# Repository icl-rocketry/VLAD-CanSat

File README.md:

# VLAD-CanSat
Repository Containing the hardware and firmware of VLAD, a stabby boi who will participate in the Mach-21 CanSat competition

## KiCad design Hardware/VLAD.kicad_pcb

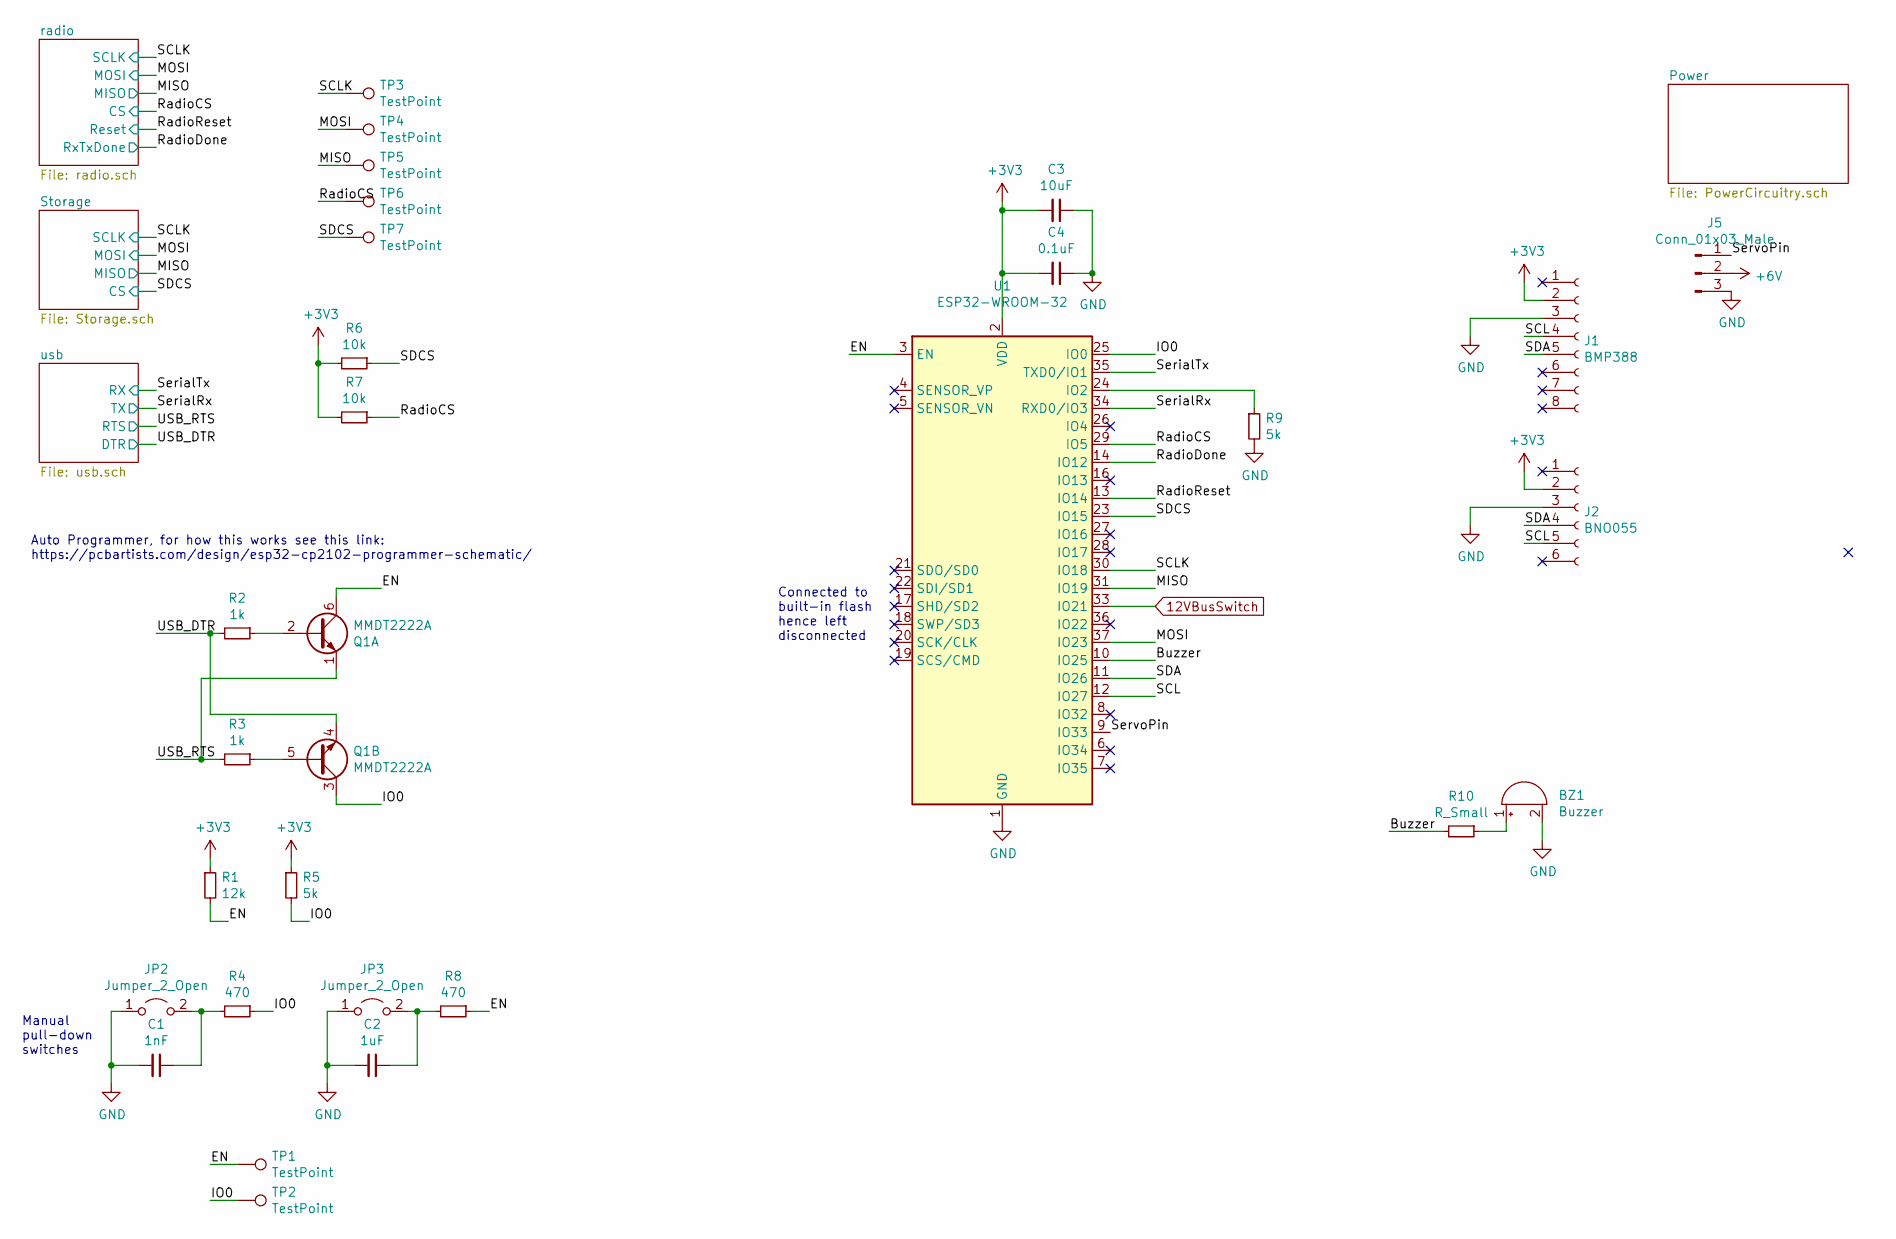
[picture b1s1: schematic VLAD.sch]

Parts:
BZ1: Buzzer; PinHeader_2x01_P2.54mm_Vertical
C1: 1nF; C_0603_1608Metric
C2: 1uF; C_0603_1608Metric
C3: 10uF; C_0603_1608Metric
C4: 0.1uF; C_0603_1608Metric
J1: BMP388; PinSocket_1x08_P2.54mm_Vertical
J2: BNO055; PinSocket_1x06_P2.54mm_Vertical
J5: Conn_01x03_Male; PinHeader_1x03_P2.54mm_Vertical
JP2, JP3: Jumper_2_Open; PinHeader_1x02_P2.54mm_Vertical
Q1: MMDT2222A; SOT-363_SC-70-6
R1: 12k; R_0603_1608Metric
R2, R3: 1k; R_0603_1608Metric
R4, R8: 470; R_0603_1608Metric
R5, R9: 5k; R_0603_1608Metric
R6, R7: 10k; R_0603_1608Metric
R10: R_Small; R_0603_1608Metric
TP1, TP2, TP3, TP4, TP5, TP6, TP7: TestPoint; TestPoint_THTPad_1.5x1.5mm_Drill0.7mm
U1: ESP32-WROOM-32

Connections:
12VBusSwitch: U1.33 (IO21); also elsewhere on the board
+3V3: C3.2, C4.2, J1.2, J2.2, R1.1, R5.1, R6.2, R7.2, U1.2 (VDD); also elsewhere on the board
+6V: J5.2; also elsewhere on the board
/Buzzer: R10.2, U1.10 (IO25)
/EN: Q1.6 (C1), R1.2, R8.1, TP1.1, U1.3 (EN)
/IO0: Q1.3 (C2), R4.1, R5.2, TP2.1, U1.25 (IO0)
/MISO: TP5.1, U1.31 (IO19); also elsewhere on the board
/MOSI: TP4.1, U1.37 (IO23); also elsewhere on the board
/RadioCS: R7.1, TP6.1, U1.29 (IO5); also elsewhere on the board
/RadioDone: U1.14 (IO12); also elsewhere on the board
/RadioReset: U1.13 (IO14); also elsewhere on the board
/SCL: J1.4, J2.5, U1.12 (IO27)
/SCLK: TP3.1, U1.30 (IO18); also elsewhere on the board
/SDA: J1.5, J2.4, U1.11 (IO26)
/SDCS: R6.1, TP7.1, U1.23 (IO15); also elsewhere on the board
/SerialRx: U1.34 (RXD0/IO3); also elsewhere on the board
/SerialTx: U1.35 (TXD0/IO1); also elsewhere on the board
/ServoPin: J5.1, U1.9 (IO33)
/USB_DTR: Q1.4 (E2), R2.2; also elsewhere on the board
/USB_RTS: Q1.1 (E1), R3.2; also elsewhere on the board
GND: BZ1.2 (+), C1.2, C2.2, C3.1, C4.1, J1.3, J2.3, J5.3, JP2.1 (A), JP3.1 (A), R9.2, U1.1 (GND), U1.15 (GND), U1.38 (GND), U1.39 (GND); also elsewhere on the board
unnamed: BZ1.1 (-), R10.1
unnamed: C1.1, JP2.2 (B), R4.2
unnamed: C2.1, JP3.2 (B), R8.2
unnamed: Q1.2 (B1), R2.1
unnamed: Q1.5 (B2), R3.1
unnamed: R9.1, U1.24 (IO2)

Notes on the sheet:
Connected to built-in flash hence left disconnected
Auto Programmer, for how this works see this link: https://pcbartists.com/design/esp32-cp2102-programmer-schematic/
Manual pull-down switches

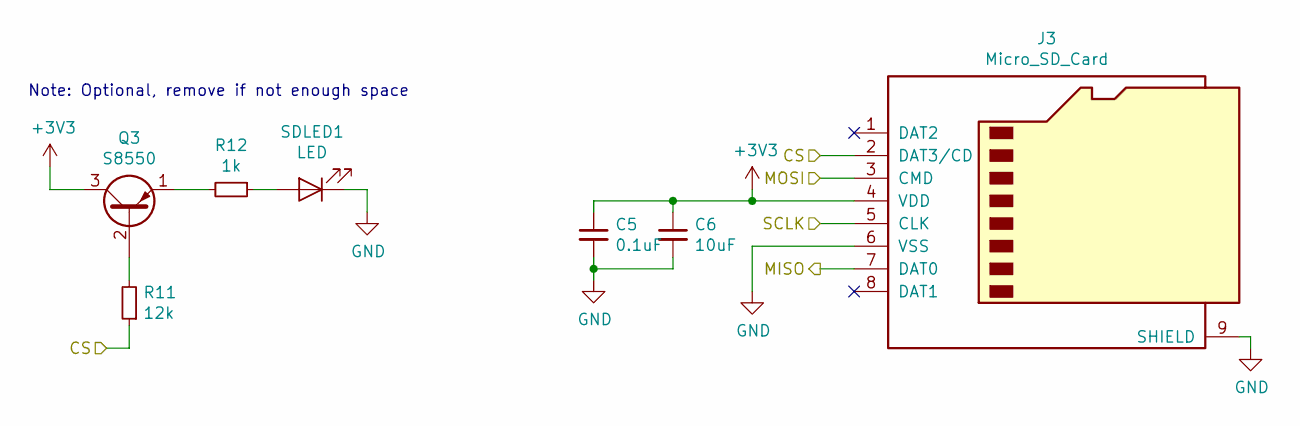
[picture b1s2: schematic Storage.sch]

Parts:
C5: 0.1uF; C_0603_1608Metric
C6: 10uF; C_0603_1608Metric
J3: Micro_SD_Card; microSD_HC_Hirose_DM3AT-SF-PEJM5
Q3: S8550; TO-92_Inline
R11: 12k; R_0603_1608Metric
R12: 1k; R_0603_1608Metric
SDLED1: LED; LED_0603_1608Metric

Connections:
+3V3: C5.1, C6.1, J3.4 (VDD), Q3.3 (C); also elsewhere on the board
/MISO: J3.7 (DAT0); also elsewhere on the board
/MOSI: J3.3 (CMD); also elsewhere on the board
/SCLK: J3.5 (CLK); also elsewhere on the board
/SDCS: J3.2 (DAT3/CD), R11.1; also elsewhere on the board
GND: C5.2, C6.2, J3.6 (VSS), J3.9 (SHIELD), SDLED1.1 (K); also elsewhere on the board
unnamed: Q3.1 (E), R12.2
unnamed: Q3.2 (B), R11.2
unnamed: R12.1, SDLED1.2 (A)

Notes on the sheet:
Note: Optional, remove if not enough space

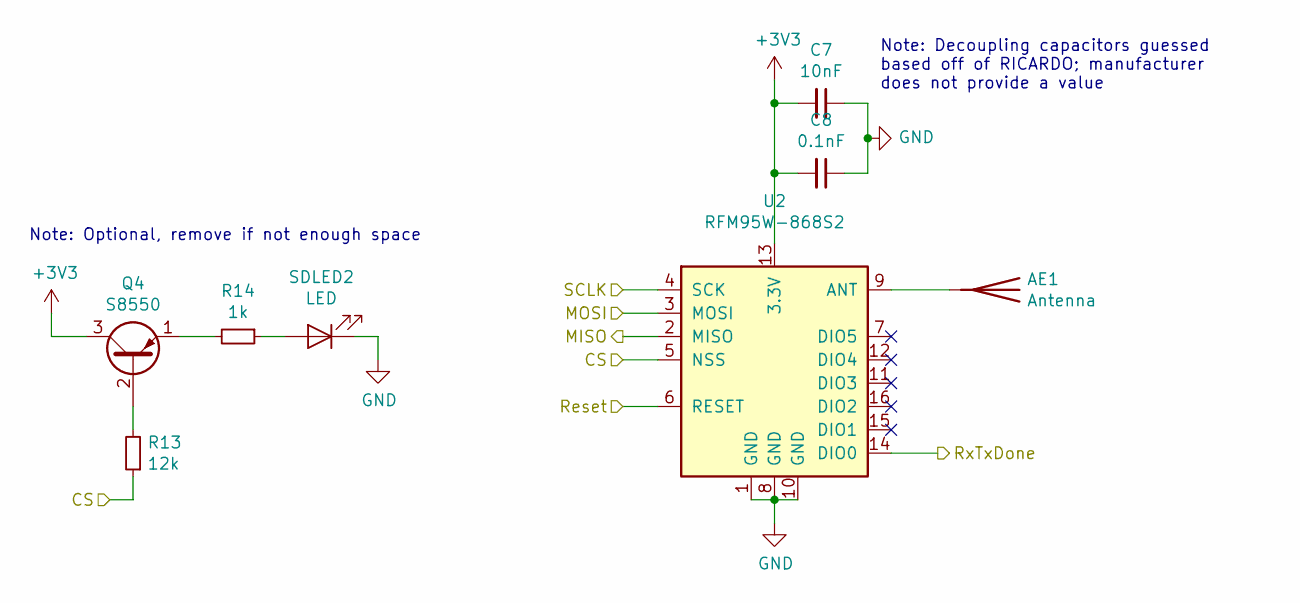
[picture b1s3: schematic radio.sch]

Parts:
AE1: Antenna; Pin_D1.1mm_L8.5mm_W2.5mm_FlatFork
C7: 10nF; C_0603_1608Metric
C8: 0.1nF; C_0603_1608Metric
Q4: S8550; TO-92_Inline
R13: 12k; R_0603_1608Metric
R14: 1k; R_0603_1608Metric
SDLED2: LED; LED_0603_1608Metric
U2: RFM95W-868S2; HOPERF_RFM9XW_SMD

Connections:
+3V3: C7.2, C8.2, Q4.3 (C), U2.13 (3.3V); also elsewhere on the board
/MISO: U2.2 (MISO); also elsewhere on the board
/MOSI: U2.3 (MOSI); also elsewhere on the board
/RadioCS: R13.1, U2.5 (NSS); also elsewhere on the board
/RadioDone: U2.14 (DIO0); also elsewhere on the board
/RadioReset: U2.6 (RESET); also elsewhere on the board
/SCLK: U2.4 (SCK); also elsewhere on the board
GND: C7.1, C8.1, SDLED2.1 (K), U2.1 (GND), U2.8 (GND), U2.10 (GND); also elsewhere on the board
unnamed: AE1.1, U2.9 (ANT)
unnamed: Q4.1 (E), R14.2
unnamed: Q4.2 (B), R13.2
unnamed: R14.1, SDLED2.2 (A)

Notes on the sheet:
Note: Decoupling capacitors guessed based off of RICARDO; manufacturer does not provide a value
Note: Optional, remove if not enough space

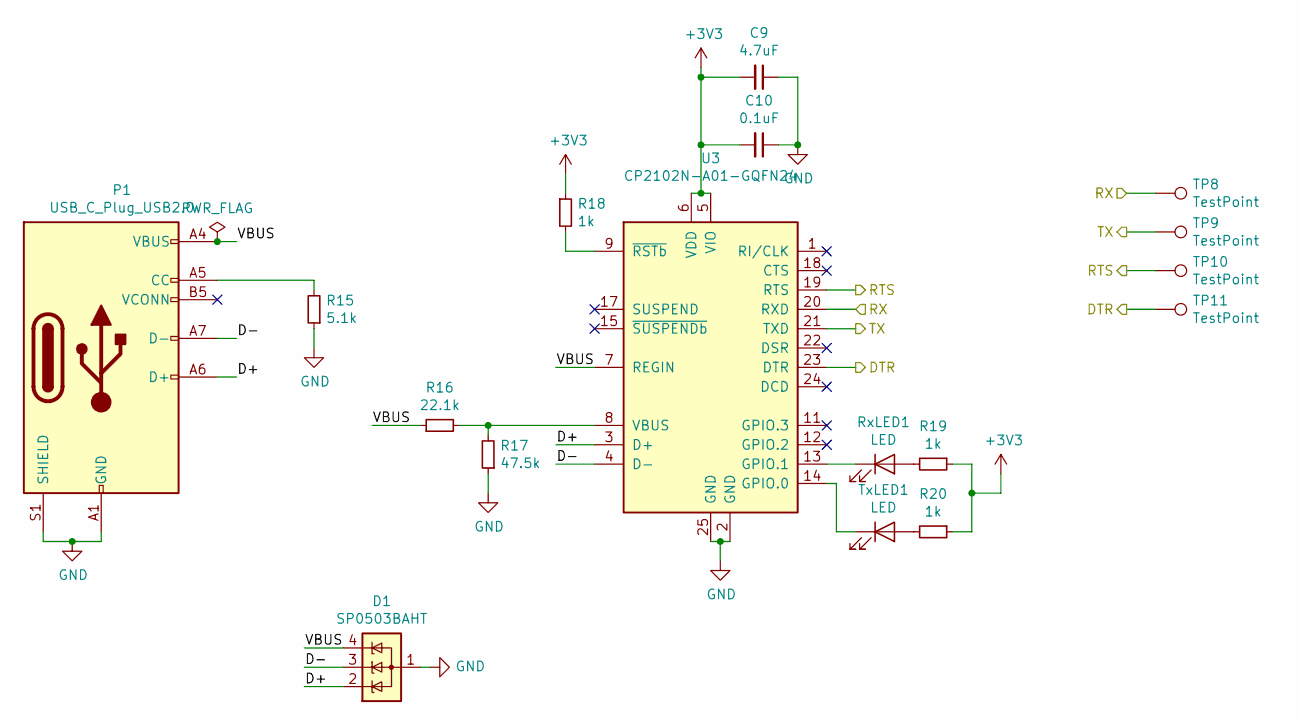
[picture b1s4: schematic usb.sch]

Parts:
C9: 4.7uF; C_0603_1608Metric
C10: 0.1uF; C_0603_1608Metric
D1: SP0503BAHT; SOT-143
P1: USB_C_Plug_USB2.0; USB_C_Receptacle_GCT_USB4085
R15: 5.1k; R_0603_1608Metric
R16: 22.1k; R_0603_1608Metric
R17: 47.5k; R_0603_1608Metric
R18, R19, R20: 1k; R_0603_1608Metric
RxLED1: LED; LED_0603_1608Metric
TP8, TP9, TP10, TP11: TestPoint; TestPoint_THTPad_1.5x1.5mm_Drill0.7mm
TxLED1: LED; LED_0603_1608Metric
U3: CP2102N-A01-GQFN24; QFN-24-1EP_4x4mm_P0.5mm_EP2.6x2.6mm

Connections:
+3V3: C9.2, C10.2, R18.1, R19.1, R20.1, U3.5 (VIO), U3.6 (VDD); also elsewhere on the board
/SerialRx: TP9.1, U3.21 (TXD); also elsewhere on the board
/SerialTx: TP8.1, U3.20 (RXD); also elsewhere on the board
/USB_DTR: TP11.1, U3.23 (DTR); also elsewhere on the board
/USB_RTS: TP10.1, U3.19 (RTS); also elsewhere on the board
/usb/D+: D1.2 (K), P1.A6 (D+), U3.3 (D+)
/usb/D-: D1.3 (K), P1.A7 (D-), U3.4 (D-)
/usb/VBUS: D1.4 (K), P1.A4 (VBUS), P1.A9 (VBUS), P1.B4 (VBUS), P1.B9 (VBUS), R16.1, U3.7 (REGIN)
GND: C9.1, C10.1, D1.1 (A), P1.A1 (GND), P1.A12 (GND), P1.B1 (GND), P1.B12 (GND), P1.S1 (SHIELD), R15.1, R17.1, U3.2 (GND), U3.25 (GND); also elsewhere on the board
unnamed: P1.A5 (CC), R15.2
unnamed: R16.2, R17.2, U3.8 (VBUS)
unnamed: R18.2, U3.9 (~RSTb)
unnamed: R19.2, RxLED1.2 (A)
unnamed: R20.2, TxLED1.2 (A)
unnamed: RxLED1.1 (K), U3.13 (GPIO.1)
unnamed: TxLED1.1 (K), U3.14 (GPIO.0)

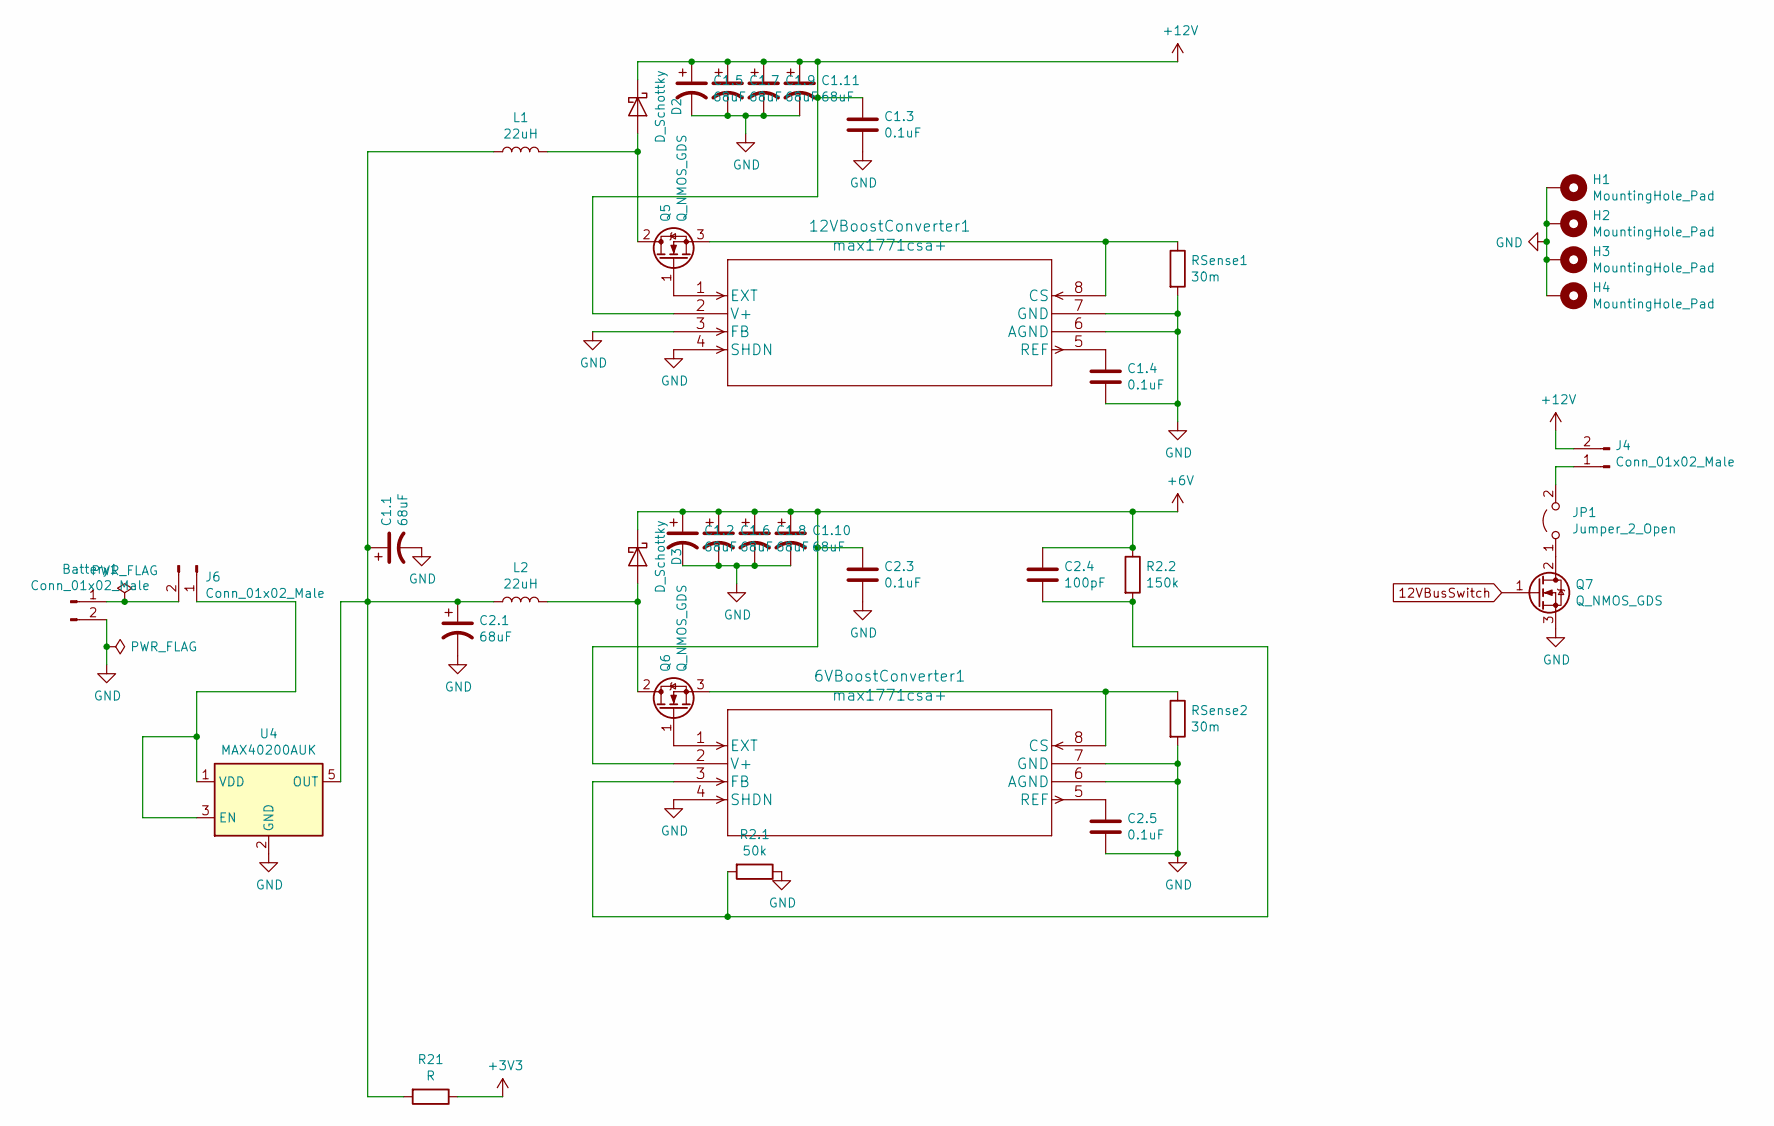
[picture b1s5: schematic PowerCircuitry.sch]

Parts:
6VBoostConverter1, 12VBoostConverter1: max1771csa+; MAX1771CSA&plus_
Battery1: Conn_01x02_Male; JST_EH_B2B-EH-A_1x02_P2.50mm_Vertical
C1.1, C1.2, C1.5, C1.6, C1.7, C1.8, C1.9, C1.10, C1.11, C2.1: 68uF; CP_Radial_D6.3mm_P2.50mm
C1.3, C1.4, C2.3, C2.5: 0.1uF; C_0603_1608Metric
C2.4: 100pF; C_0603_1608Metric
D2, D3: D_Schottky; D_SOD-123F
H1, H2, H3, H4: MountingHole_Pad; MountingHole_4mm_Pad
J4: Conn_01x02_Male; PinHeader_2x01_P2.54mm_Vertical
J6: Conn_01x02_Male; PinHeader_1x02_P2.54mm_Vertical
JP1: Jumper_2_Open; PinHeader_1x02_P2.54mm_Vertical
L1, L2: 22uH; L_Toroid_Vertical_L16.0mm_W8.0mm_P7.62mm
Q5, Q6, Q7: Q_NMOS_GDS; SOT-23
R2.1: 50k; R_0603_1608Metric
R2.2: 150k; R_0603_1608Metric
R21: R; R_Axial_DIN0204_L3.6mm_D1.6mm_P1.90mm_Vertical
RSense1, RSense2: 30m; R_0603_1608Metric
U4: MAX40200AUK; SOT-23-5

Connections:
12VBusSwitch: Q7.1 (G); also elsewhere on the board
+3V3: R21.1; also elsewhere on the board
+6V: 6VBoostConverter1.2 (V+), C1.2.1, C1.6.1, C1.8.1, C1.10.1, C2.3.1, C2.4.1, D3.1 (K), R2.2.1; also elsewhere on the board
+12V: 12VBoostConverter1.2 (V+), C1.3.1, C1.5.1, C1.7.1, C1.9.1, C1.11.1, D2.1 (K), J4.2
GND: 6VBoostConverter1.4 (SHDN), 6VBoostConverter1.6 (AGND), 6VBoostConverter1.7 (GND), 12VBoostConverter1.3 (FB), 12VBoostConverter1.4 (SHDN), 12VBoostConverter1.6 (AGND), 12VBoostConverter1.7 (GND), Battery1.2, C1.1.2, C1.2.2, C1.3.2, C1.4.2, C1.5.2, C1.6.2, C1.7.2, C1.8.2, C1.9.2, C1.10.2, C1.11.2, C2.1.2, C2.3.2, C2.5.2, H1.1, H2.1, H3.1, H4.1, Q7.3 (S), R2.1.1, RSense1.2, RSense2.2, U4.2 (GND); also elsewhere on the board
unnamed: 6VBoostConverter1.1 (EXT), Q6.1 (G)
unnamed: 6VBoostConverter1.3 (FB), C2.4.2, R2.1.2, R2.2.2
unnamed: 6VBoostConverter1.5 (REF), C2.5.1
unnamed: 6VBoostConverter1.8 (CS), Q6.3 (S), RSense2.1
unnamed: 12VBoostConverter1.1 (EXT), Q5.1 (G)
unnamed: 12VBoostConverter1.5 (REF), C1.4.1
unnamed: 12VBoostConverter1.8 (CS), Q5.3 (S), RSense1.1
unnamed: Battery1.1, J6.2
unnamed: C1.1.1, C2.1.1, L1.1, L2.1, R21.2, U4.5 (OUT)
unnamed: D2.2 (A), L1.2, Q5.2 (D)
unnamed: D3.2 (A), L2.2, Q6.2 (D)
unnamed: J4.1, JP1.2 (B)
unnamed: J6.1, U4.1 (VDD), U4.3 (EN)
unnamed: JP1.1 (A), Q7.2 (D)

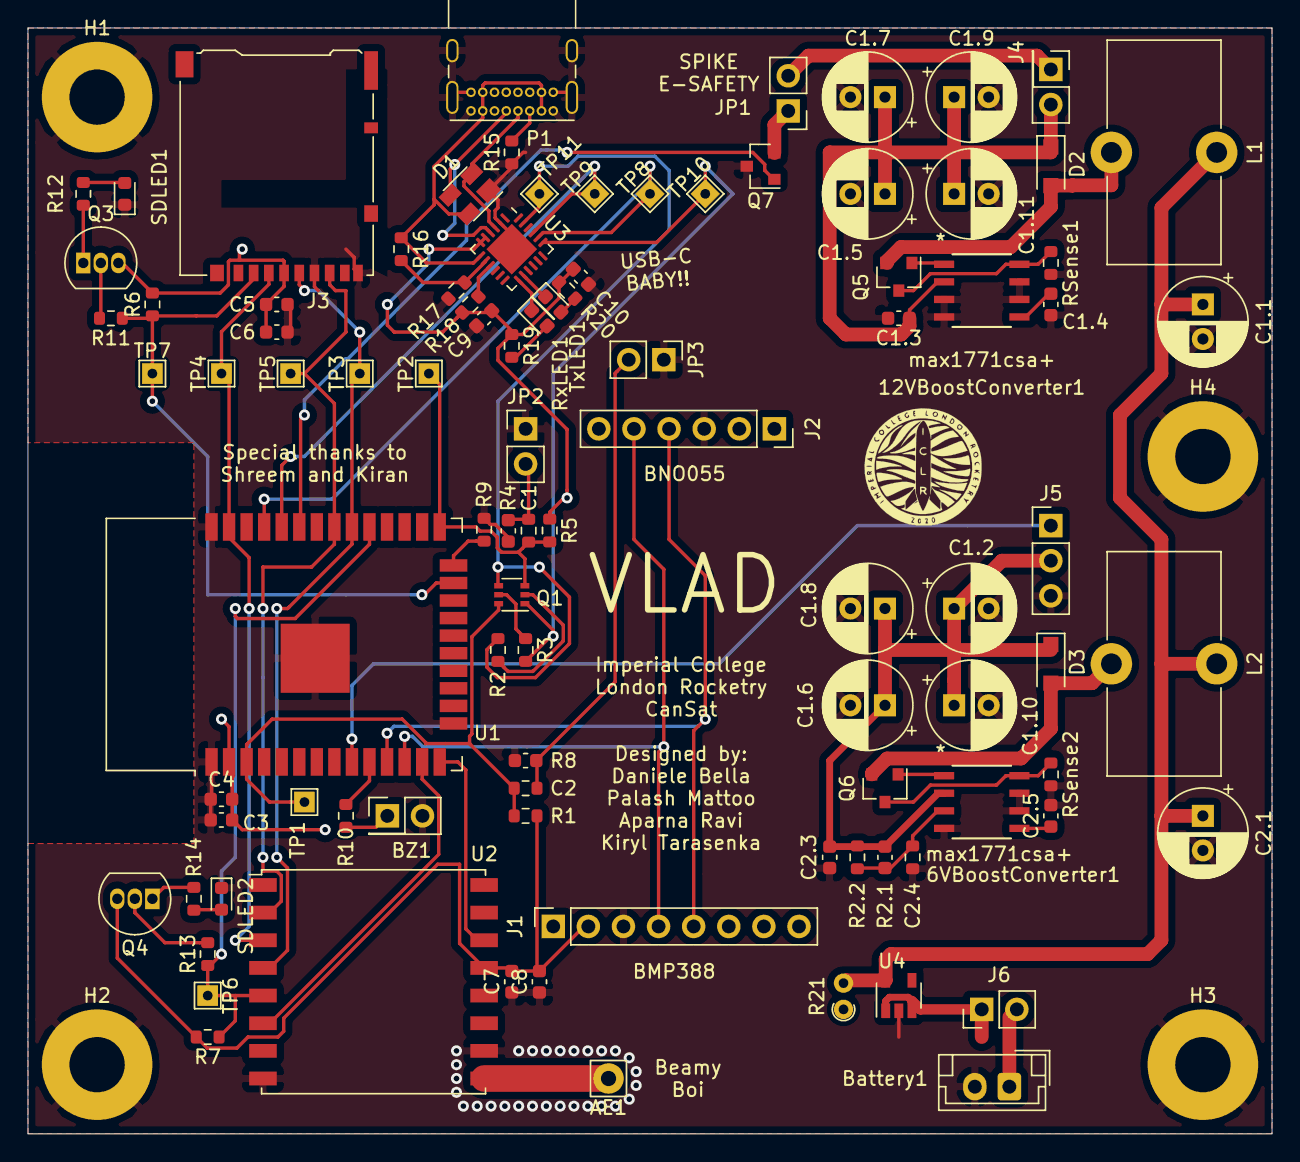
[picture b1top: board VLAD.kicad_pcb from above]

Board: 2 copper layers, 90.0 x 80.0 mm, 99 parts (0 on the bottom side), 59 nets.

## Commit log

2021-04-03 Initialised KiCAD project
2021-04-03 Added ESP32 Chip, powered it, and created SPI component sheets
2021-04-03 Created Radio Schematic
2021-04-03 Connected radio to ESP32
2021-04-07 Switched antenna from SMA connector to through-hole
2021-04-07 Added comment about decoupling capacitors
2021-04-10 Removed backup files from repo and added .gitignore
2021-04-13 Added no-connection flag to internal flash pins
2021-04-13 Fixed switched value and name on EN pin for ESP32
2021-04-13 Added SD card holder and circuitry
2021-04-13 Added connections from SD card to ESP32
2021-04-14 Added USB circuitry
2021-04-14 Added circuitry to program ESP32
2021-04-14 Added connector to program using external FTDI chip
2021-04-14 Added connectors to SPI pins for debugging
2021-04-14 Added activity LEDs for SD and radio
2021-04-17 Selected some footprints
2021-04-17 Manually merged power to main
    Might have some problems with USB
2021-04-17 Re-added Max1771 IC
    By copy pasting
2021-04-17 Fixed project specific library naming
2021-04-17 Added master switch etc
    I don't like MOSFETs
2021-04-17 Added test points everywhere
2021-04-17 Added pull-ups to CS pins
2021-04-18 Added Buzzer
2021-04-18 Added temporary sensor connections
2021-04-18 Fixed some of the ERC errors
2021-04-18 Created PCB file and laid out components
2021-04-18 Routed PCB
2021-04-19 Final changes for this first draft
2021-05-15 Genuine Confusion
    Changed to an ideal diode whatever tf that is
2021-05-15 Need to change pin headers for servo
    Unsure at this stage, will look into which transistors etc to use.
2021-05-18 Fixed minor issue with pin
2021-05-18 Changed 300uF to 4x68uF
    Cos why not
2021-05-20 Split PCB setup
    Setup the PCB with each section split. J5 didn't have a schematic so I picked one.
2021-05-21 PCB, main ESP32 stuff
    My section of the wiring, left some stuff for the top ground fill and for other sections top wires. Could probably tighten the design in some areas.
2021-05-21 Fixed some footprints
    Things to bring up:
    1. Used a 2N2219 BJT (?) transistor for the sake of circuit connection and footprint. IRL would be using either a 2N2222 (which Palash has in stock) or the one linked on the excel sheet.
    2. Used a resistor to break 3.3V bus from the node to prevent wrong connections. IRL will just use a breadboard wire to bridge it, unless more elegant ways of doing this.
    3. Need to sort out the global connection bs idk how to do that.
2021-05-21 Power PCB rough layout
    Bro im new at this pls save me
2021-05-22 Added 90mm x 90mm outline and rough layout
    I uh don't know how to delete lines lol I hope there's a way otherwise we will have to redo some stuff.
    Also I think the capacitors and inductors etc etc are taking up a lot of space. They may need new footprints
2021-05-22 Fixed N-Channel MOSFET, etc
    And a few net label tings
2021-05-22 Put EVERYTHING in the 90x90 space
    Ofc need to sort out the rats nest better. Nearly there
2021-05-25 Some connections
    I hope this is ok
2021-05-25 Added lots of things - needs some redoing
    Fun, but ffs could have been easier
2021-05-26 Added bunch of vias
    Now need to connect some more tracks up and we're good to proceed to adding ground planes etc. Also decreased the size of the board to fit within 90mm x 80mm, have further opportunities to potentiall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
2021-05-27 Not much new
2021-05-28 Tracks done (albeit OCDifying)
    All tracks are done in the sense that everything has found a routing, some components still may need to be moved though, such as the sensors on board and the push switches.
    Antenna stuff needs doing.
    Board may need to be reshaped (keepout zone?).
    GND plane needs to be added + silkscreens + memes
2021-05-29 Added GND plane and 3V3 plane
    4 connections left to make, not sure what the issue is with some of them...
2021-05-29 Fixed all tracks
    yay
2021-05-29 Re-did some no-fill zones
    For SD card
2021-05-29 Need some THT - SMD changes
    Inductors, capacitors, MAX1771CSA, the LED dudes and the ones next to the ESP
2021-06-01 Fixed RF transceiver
2021-06-01 Tried to add footprints. Emphasis on tried.
2021-06-01 Executive decision to use THT capacitors
    THT >>>>>>>>>>>> SMD
2021-06-01 Traccs done, meme time
    Need to fix the silkscreen stuff for the components and also the back silkscreen memes etc.
2021-06-01 Added Silkscreens
2021-06-19 Added firmware folder, initialised pio, defined structure
2021-06-19 Test for branch
    I em simple person i ned to chec
2021-06-20 Some work on sensors
2021-06-22 Added code snippets to populate later
    Need to first learn how the code actually works in C++ and also figure out a way to externally test it.
2021-06-26 hello this is a test
    :)
2021-06-29 Testing
2021-07-05 Copied state machine from DAQ firmware
2021-07-05 Added state machine code to main.cpp
2021-07-05 Added exitState function to state machine
2021-07-05 Added Skeletion of Radio.h
2021-07-05 Added GCS firmware
2021-07-06 set up header skeleton
2021-07-06 servo cpp
    created servo cpp file
2021-07-06 set up servo cpp skeleton
2021-07-06 defining actions for servo
    Outlined 3 main actions: deploying legs, retracting spike, retracting legs. Required times and speeds of servo to be found through manual testing.
2021-07-07 Made the thing compile baby
2021-07-07 Added cpp files for the other states
2021-07-08 Added Accelerometer code and adjusted Barom code
2021-07-08 Sd card logging
2021-07-08 Cause I forgot to save -_-
2021-07-08 Got code to compile but missing bits
    Still missing BNO, BMP and Error handling integration
2021-07-09 servo cpp syntax
    added a semi-colon to the move_servo() func
2021-07-09 defining some undefined functions, variables
    just moving things in cpp to header file also
2021-07-09 Added pin definition header file
2021-07-09 Added everything but sendTelemetry and header reading
    Need to set packet structure in stone first
2021-07-10 implementing enums
    trying to clean code up with enum
2021-07-10 Made minor changes
    It works!!!
2021-07-10 enums in h file
2021-07-10 fixed syntax errors to make it compile
2021-07-10 Added syntax for overload
2021-07-10 test commit
2021-07-10 created move_request function
    allows us to interact with the library elsewhere
2021-07-10 Implemented and tested request_move
2021-07-10 attach to pin
    attaches to SERVO_PIN within begin() function
2021-07-10 added switch
    Switched ;) from if statements to switch statement
2021-07-10 added buzzer() in public
2021-07-10 Made hopefully working radio
2021-07-10 Configured ESP32 and fixed typo
2021-07-10 Added Spike Code
2021-07-10 Change to BNO085
2021-07-10 Created skeleton of serialInterface class
2021-07-10 update libs
2021-07-10 more libs
2021-07-10 removed delay and added code for latch deployment
    unfinished code for error handling and state machine
    fixed :: and . mistakes
2021-07-10 added header files
    also made error alert extra annoying
2021-07-10 changed type for 'delay'
2021-07-10 little changes to test compile
2021-07-10 added stateAlert to state codes
2021-07-10 Readded missing ESP32 Servo library
    Previously stopped compilation
2021-07-10 Error Handling code (to be tested)
2021-07-11 Corrected servo library present
2021-07-11 GCS in compilable state
2021-07-11 Fixed syntax errors
2021-07-11 Fixed runtime errors
2021-07-11 Implemented _txDone Check
2021-07-11 updated getOrientation fun
2021-07-11 completed error handling buzzer code
2021-07-11 Fixed syntax errors, allowing code to compile
2021-07-11 Fixed syntax error and added library
2021-07-11 Made buzzer code compile and started integration
2021-07-11 Added include guards to esp32_tone library
2021-07-12 Added sensors to logging code
    Fixed minor issue with error handling type names
2021-07-12 Made classes raise errors as appropriate
2021-07-12 Made more classes buzz the buzzer in the case of an error
2021-07-12 Made error buzzer code simpler
2021-07-12 fixed buzzer class
2021-07-12 small changes
    added real part of quaternian, and changed headers in SDcontrolfile
2021-07-12 Added class instances to statemachine
2021-07-12 integrated radio with sensors and data input
2021-07-12 Removed ESP32_tone library
    Coded better implementation
    thx Kirnan <3
2021-07-12 Made spike raise flag when it fires
2021-07-12 Moved sensors to the correct i2c pins
2021-07-12 Code to be tested
2021-07-12 Made basic wifi interface
2021-07-12 Added telemetry logging
2021-07-12 Finalised wifi interface
2021-07-12 Troubleshooting kernel panics
2021-07-13 Troubleshot IMU some more
    Need to rewrite IMU class
2021-07-13 Coded functional build
    Lacking IMU and baro, but it is 4AM
2021-07-13 attempt numero uno
2021-07-13 Fixed display of orientation
2021-07-13 Added RSSI to outputs
2021-07-13 Made the libraries pace themselves
2021-07-13 MPU
    I think this is all for the MPU, might be some errors.
2021-07-15 late night vibes
2021-07-15 Yeet
2021-07-15 Hacked servo in instead of spike
2021-07-15 Modified states
2021-07-15 Added error flags

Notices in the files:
parts and their libraries:
Copyright 2016 Accelerated Designs. All rights reserved.
